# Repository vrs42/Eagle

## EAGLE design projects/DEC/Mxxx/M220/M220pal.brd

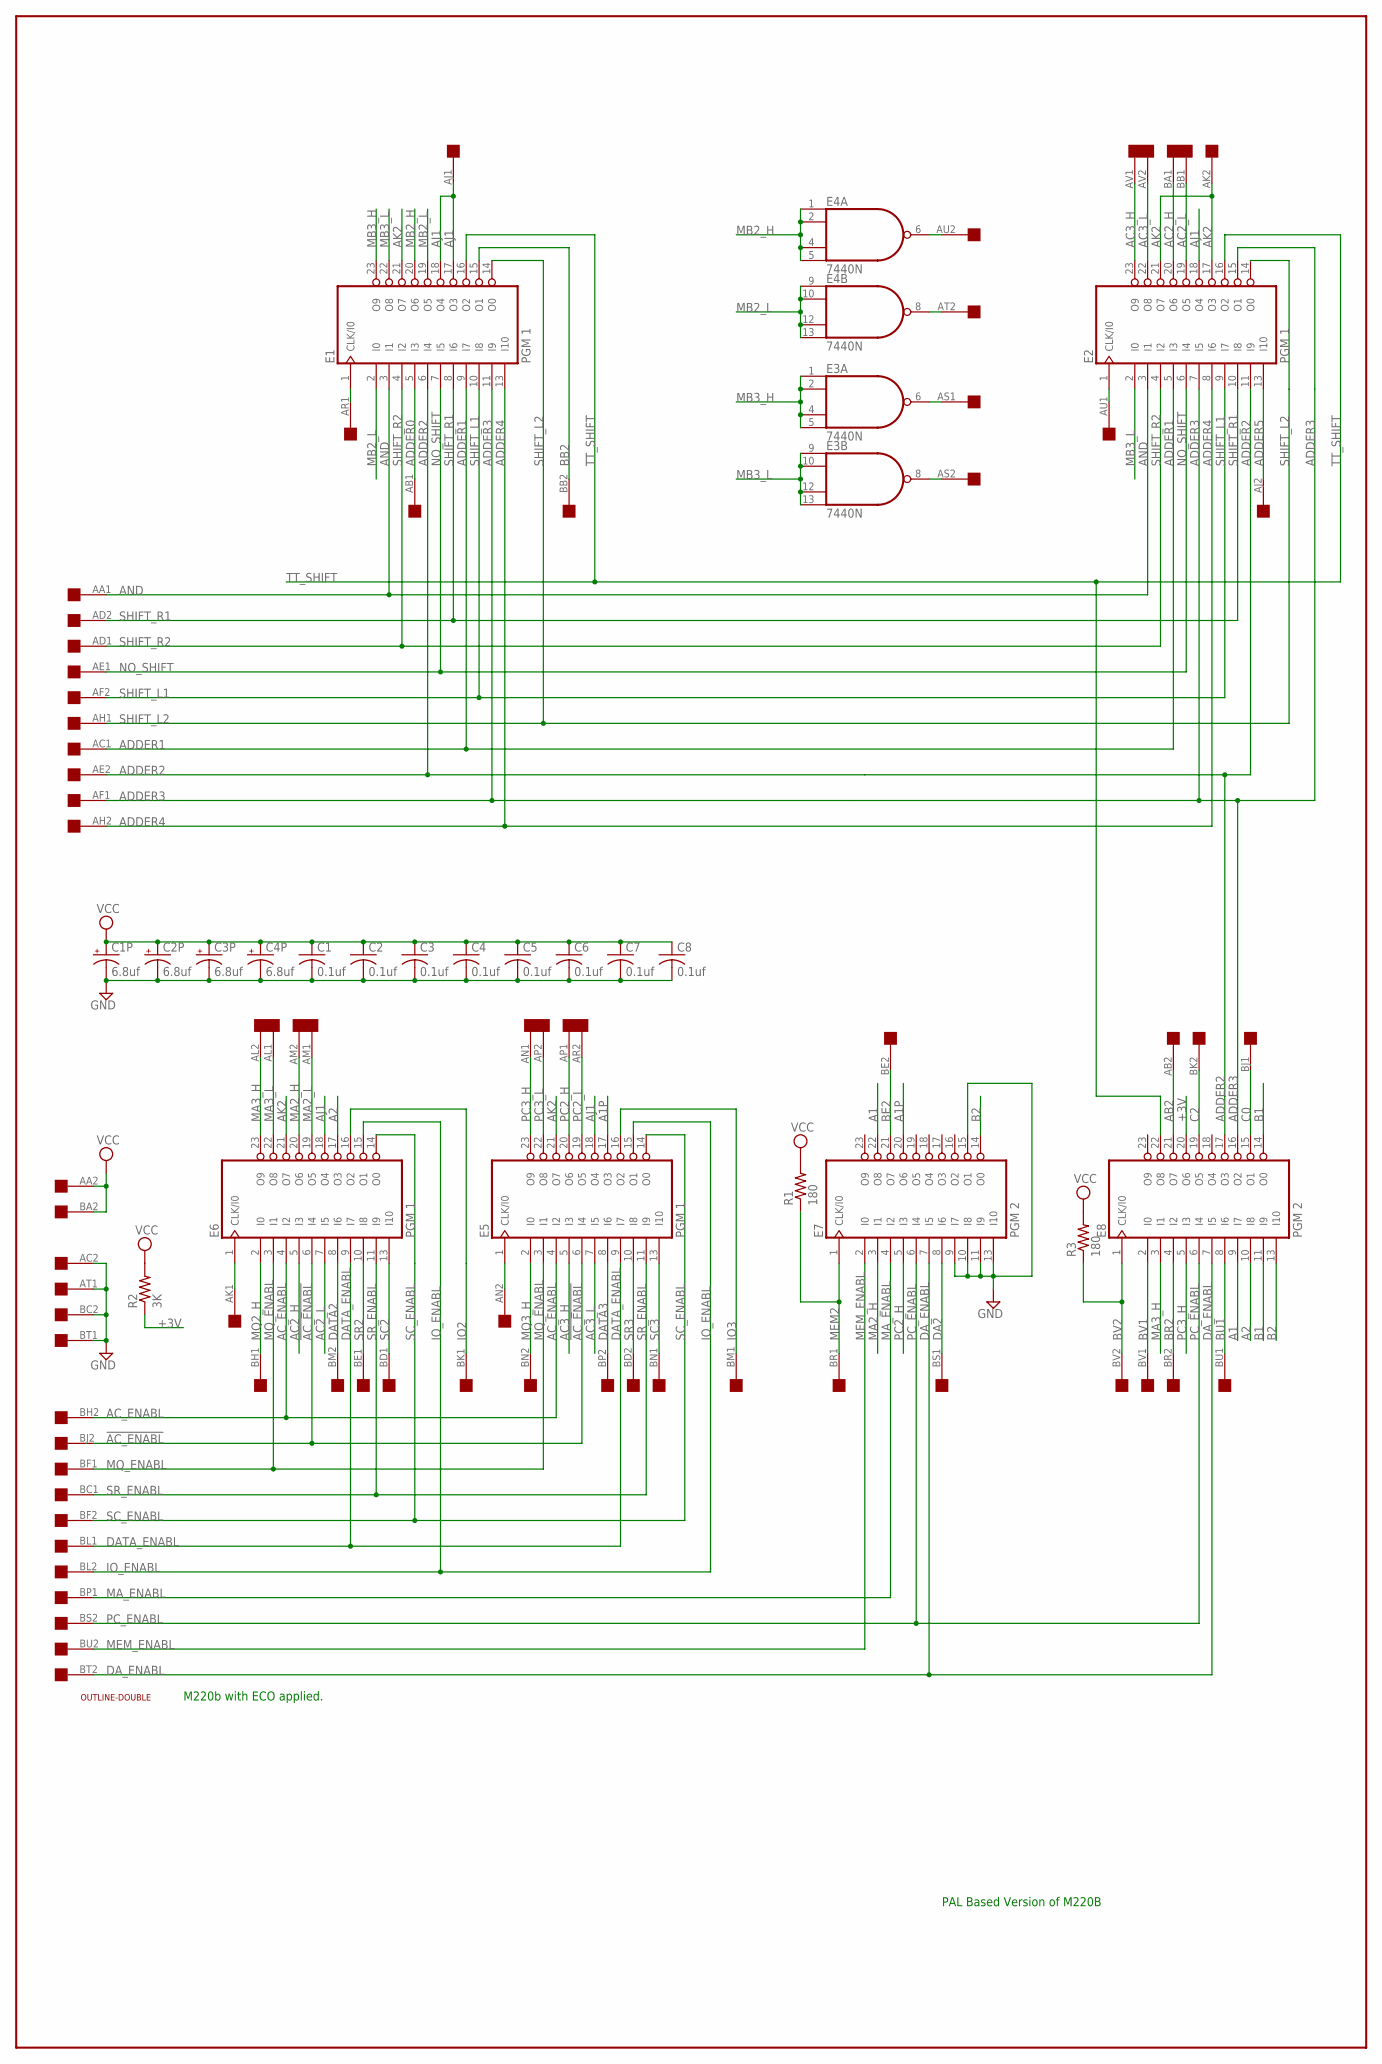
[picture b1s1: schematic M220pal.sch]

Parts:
C1, C2, C3, C4, C5, C6, C7, C8: 0.1uf; C050-025X075
C1P, C2P, C3P, C4P: 6.8uf; E15-5
E1, E2, E5, E6: PGM 1; DIL24-3
E3, E4: 7440N; DIL14
E7, E8: PGM 2; DIL24-3
R1, R3: 180; 0207/10
R2: 3K; 0207/10
U$1: DOUBLE; EDGE-CON4
U$2: OUTLINE-DOUBLE; DOUBLE

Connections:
!AC_ENABL: E5.6 (I4), E6.6 (I4), U$1.BJ2
+3V: E8.20 (O6), R2.1
A1: E7.22 (O8), E8.9 (I7)
A1P: E5.17 (O3), E7.20 (O6)
A2: E6.17 (O3), E8.10 (I8)
AB2: E8.21 (O7), U$1.AB2
AC2_H: E2.20 (O6), E6.5 (I3), U$1.BA1
AC2_L: E2.19 (O5), E6.7 (I5), U$1.BB1
AC3_H: E2.23 (O9), E5.5 (I3), U$1.AV1
AC3_L: E2.22 (O8), E5.7 (I5), U$1.AV2
AC_ENABL: E5.4 (I2), E6.4 (I2), U$1.BH2
ADDER0: E1.5 (I3), U$1.AB1
ADDER1: E1.9 (I7), E2.5 (I3), U$1.AC1
ADDER2: E1.6 (I4), E2.11 (I9), E8.17 (O3), U$1.AE2
ADDER3: E1.11 (I9), E2.7 (I5), E2.15 (O1), E8.16 (O2), U$1.AF1
ADDER4: E1.13 (I10), E2.8 (I6), U$1.AH2
ADDER5: E2.13 (I10), U$1.AJ2
AJ1: E1.17 (O3), E1.18 (O4), E2.18 (O4), E5.18 (O4), E6.18 (O4), U$1.AJ1
AK2: E1.21 (O7), E2.17 (O3), E2.21 (O7), E5.21 (O7), E6.21 (O7), U$1.AK2
AND: E1.3 (I1), E2.3 (I1), U$1.AA1
AS1: E3.6 (O), U$1.AS1
AS2: E3.8 (O), U$1.AS2
AT2: E4.8 (O), U$1.AT2
AU2: E4.6 (O), U$1.AU2
B1: E8.11 (I9), E8.14 (O0)
B2: E7.14 (O0), E8.13 (I10)
BB2: E1.15 (O1), U$1.BB2
BE2: E7.21 (O7), U$1.BE2
BR2: E8.4 (I2), U$1.BR2
BU1: E8.8 (I6), U$1.BU1
BV1: E8.2 (I0), U$1.BV1
BV2: E8.1 (CLK/I0), R3.1, U$1.BV2
C0: E8.15 (O1), U$1.BJ1
C2: E8.19 (O5), U$1.BK2
DA2: E7.8 (I6), U$1.BS1
DATA2: E6.8 (I6), U$1.BM2
DATA3: E5.8 (I6), U$1.BP2
DATA_ENABL: E5.9 (I7), E6.9 (I7), U$1.BL1
DA_ENABL: E7.7 (I5), E8.7 (I5), U$1.BT2
GND: C1.2, C1P.-, C2.2, C2P.-, C3.2, C3P.-, C4.2, C4P.-, C5.2, C6.2, C7.2, C8.2, E1.12 (GND), E2.12 (GND), E3.7 (GND), E4.7 (GND), E5.12 (GND), E6.12 (GND), E7.9 (I7), E7.10 (I8), E7.11 (I9), E7.12 (GND), E7.13 (I10), E7.15 (O1), E8.12 (GND), U$1.AC2, U$1.AT1, U$1.BC2, U$1.BT1
IO2: E6.16 (O2), U$1.BK1
IO3: E5.16 (O2), U$1.BM1
IO_ENABL: E5.15 (O1), E6.15 (O1), U$1.BL2
MA2_H: E6.20 (O6), E7.3 (I1), U$1.AM2
MA2_L: E6.19 (O5), U$1.AM1
MA3_H: E6.23 (O9), E8.3 (I1), U$1.AL2
MA3_L: E6.22 (O8), U$1.AL1
MA_ENABL: E7.4 (I2), U$1.BP1
MB2_H: E1.20 (O6), E4.1 (I0), E4.2 (I1), E4.4 (I2), E4.5 (I3)
MB2_L: E1.2 (I0), E1.19 (O5), E4.9 (I0), E4.10 (I1), E4.12 (I2), E4.13 (I3)
MB3_H: E1.23 (O9), E3.1 (I0), E3.2 (I1), E3.4 (I2), E3.5 (I3)
MB3_L: E1.22 (O8), E2.2 (I0), E3.9 (I0), E3.10 (I1), E3.12 (I2), E3.13 (I3)
MEM2: E7.1 (CLK/I0), R1.1, U$1.BR1
MEM_ENABL: E7.2 (I0), U$1.BU2
MQ2_H: E6.2 (I0), U$1.BH1
MQ3_H: E5.2 (I0), U$1.BN2
MQ_ENABL: E5.3 (I1), E6.3 (I1), U$1.BF1
unnamed: E6.1 (CLK/I0), U$1.AK1
unnamed: E5.1 (CLK/I0), U$1.AN2
unnamed: E1.1 (CLK/I0), U$1.AR1
unnamed: E2.1 (CLK/I0), U$1.AU1
NO_SHIFT: E1.7 (I5), E2.6 (I4), U$1.AE1
PC2_H: E5.20 (O6), E7.5 (I3), U$1.AP1
PC2_L: E5.19 (O5), U$1.AR2
PC3_H: E5.23 (O9), E8.5 (I3), U$1.AN1
PC3_L: E5.22 (O8), U$1.AP2
PC_ENABL: E7.6 (I4), E8.6 (I4), U$1.BS2
SC2: E6.13 (I10), U$1.BD1
SC3: E5.13 (I10), U$1.BN1
SC_ENABL: E5.14 (O0), E6.14 (O0), U$1.BF2
SHIFT_L1: E1.10 (I8), E2.9 (I7), U$1.AF2
SHIFT_L2: E1.14 (O0), E2.14 (O0), U$1.AH1
SHIFT_R1: E1.8 (I6), E2.10 (I8), U$1.AD2
SHIFT_R2: E1.4 (I2), E2.4 (I2), U$1.AD1
SR2: E6.10 (I8), U$1.BE1
SR3: E5.10 (I8), U$1.BD2
SR_ENABL: E5.11 (I9), E6.11 (I9), U$1.BC1
TT_SHIFT: E1.16 (O2), E2.16 (O2), E8.22 (O8)
VCC: C1.1, C1P.+, C2.1, C2P.+, C3.1, C3P.+, C4.1, C4P.+, C5.1, C6.1, C7.1, C8.1, E1.24 (VCC), E2.24 (VCC), E3.14 (VCC), E4.14 (VCC), E5.24 (VCC), E6.24 (VCC), E7.24 (VCC), E8.24 (VCC), R1.2, R2.2, R3.2, U$1.AA2, U$1.BA2

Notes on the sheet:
M220b with ECO applied.
PAL Based Version of M220B

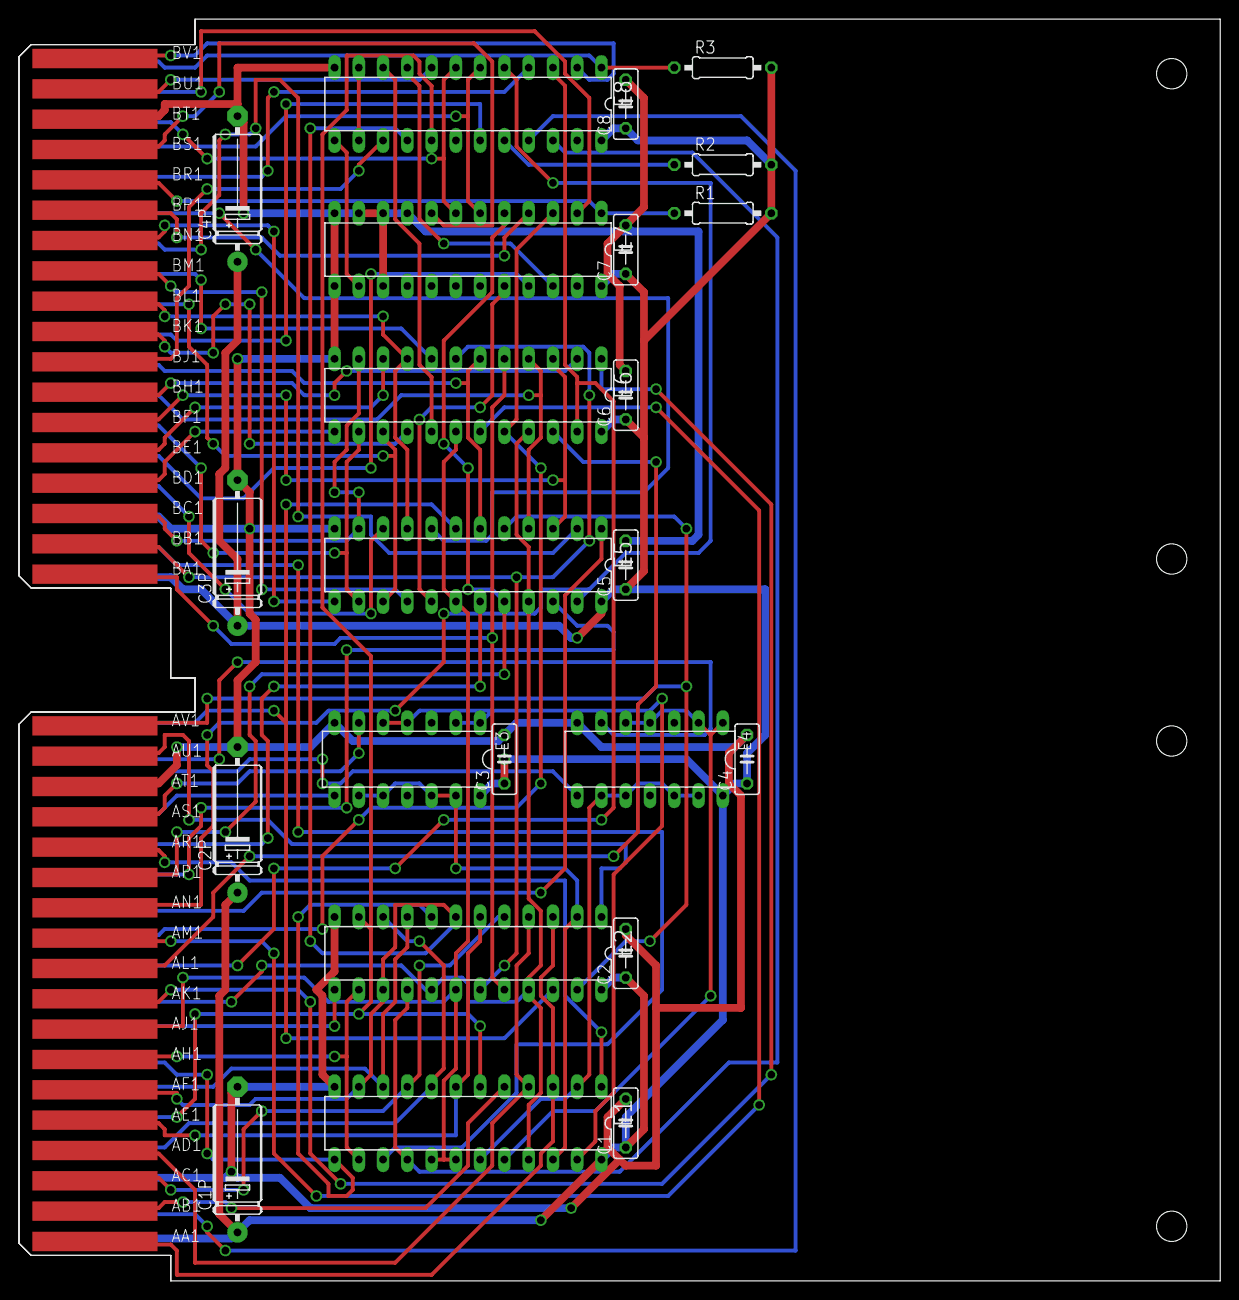
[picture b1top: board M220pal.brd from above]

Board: 2 copper layers, 125.7 x 132.1 mm, 25 parts (0 on the bottom side), 79 nets.

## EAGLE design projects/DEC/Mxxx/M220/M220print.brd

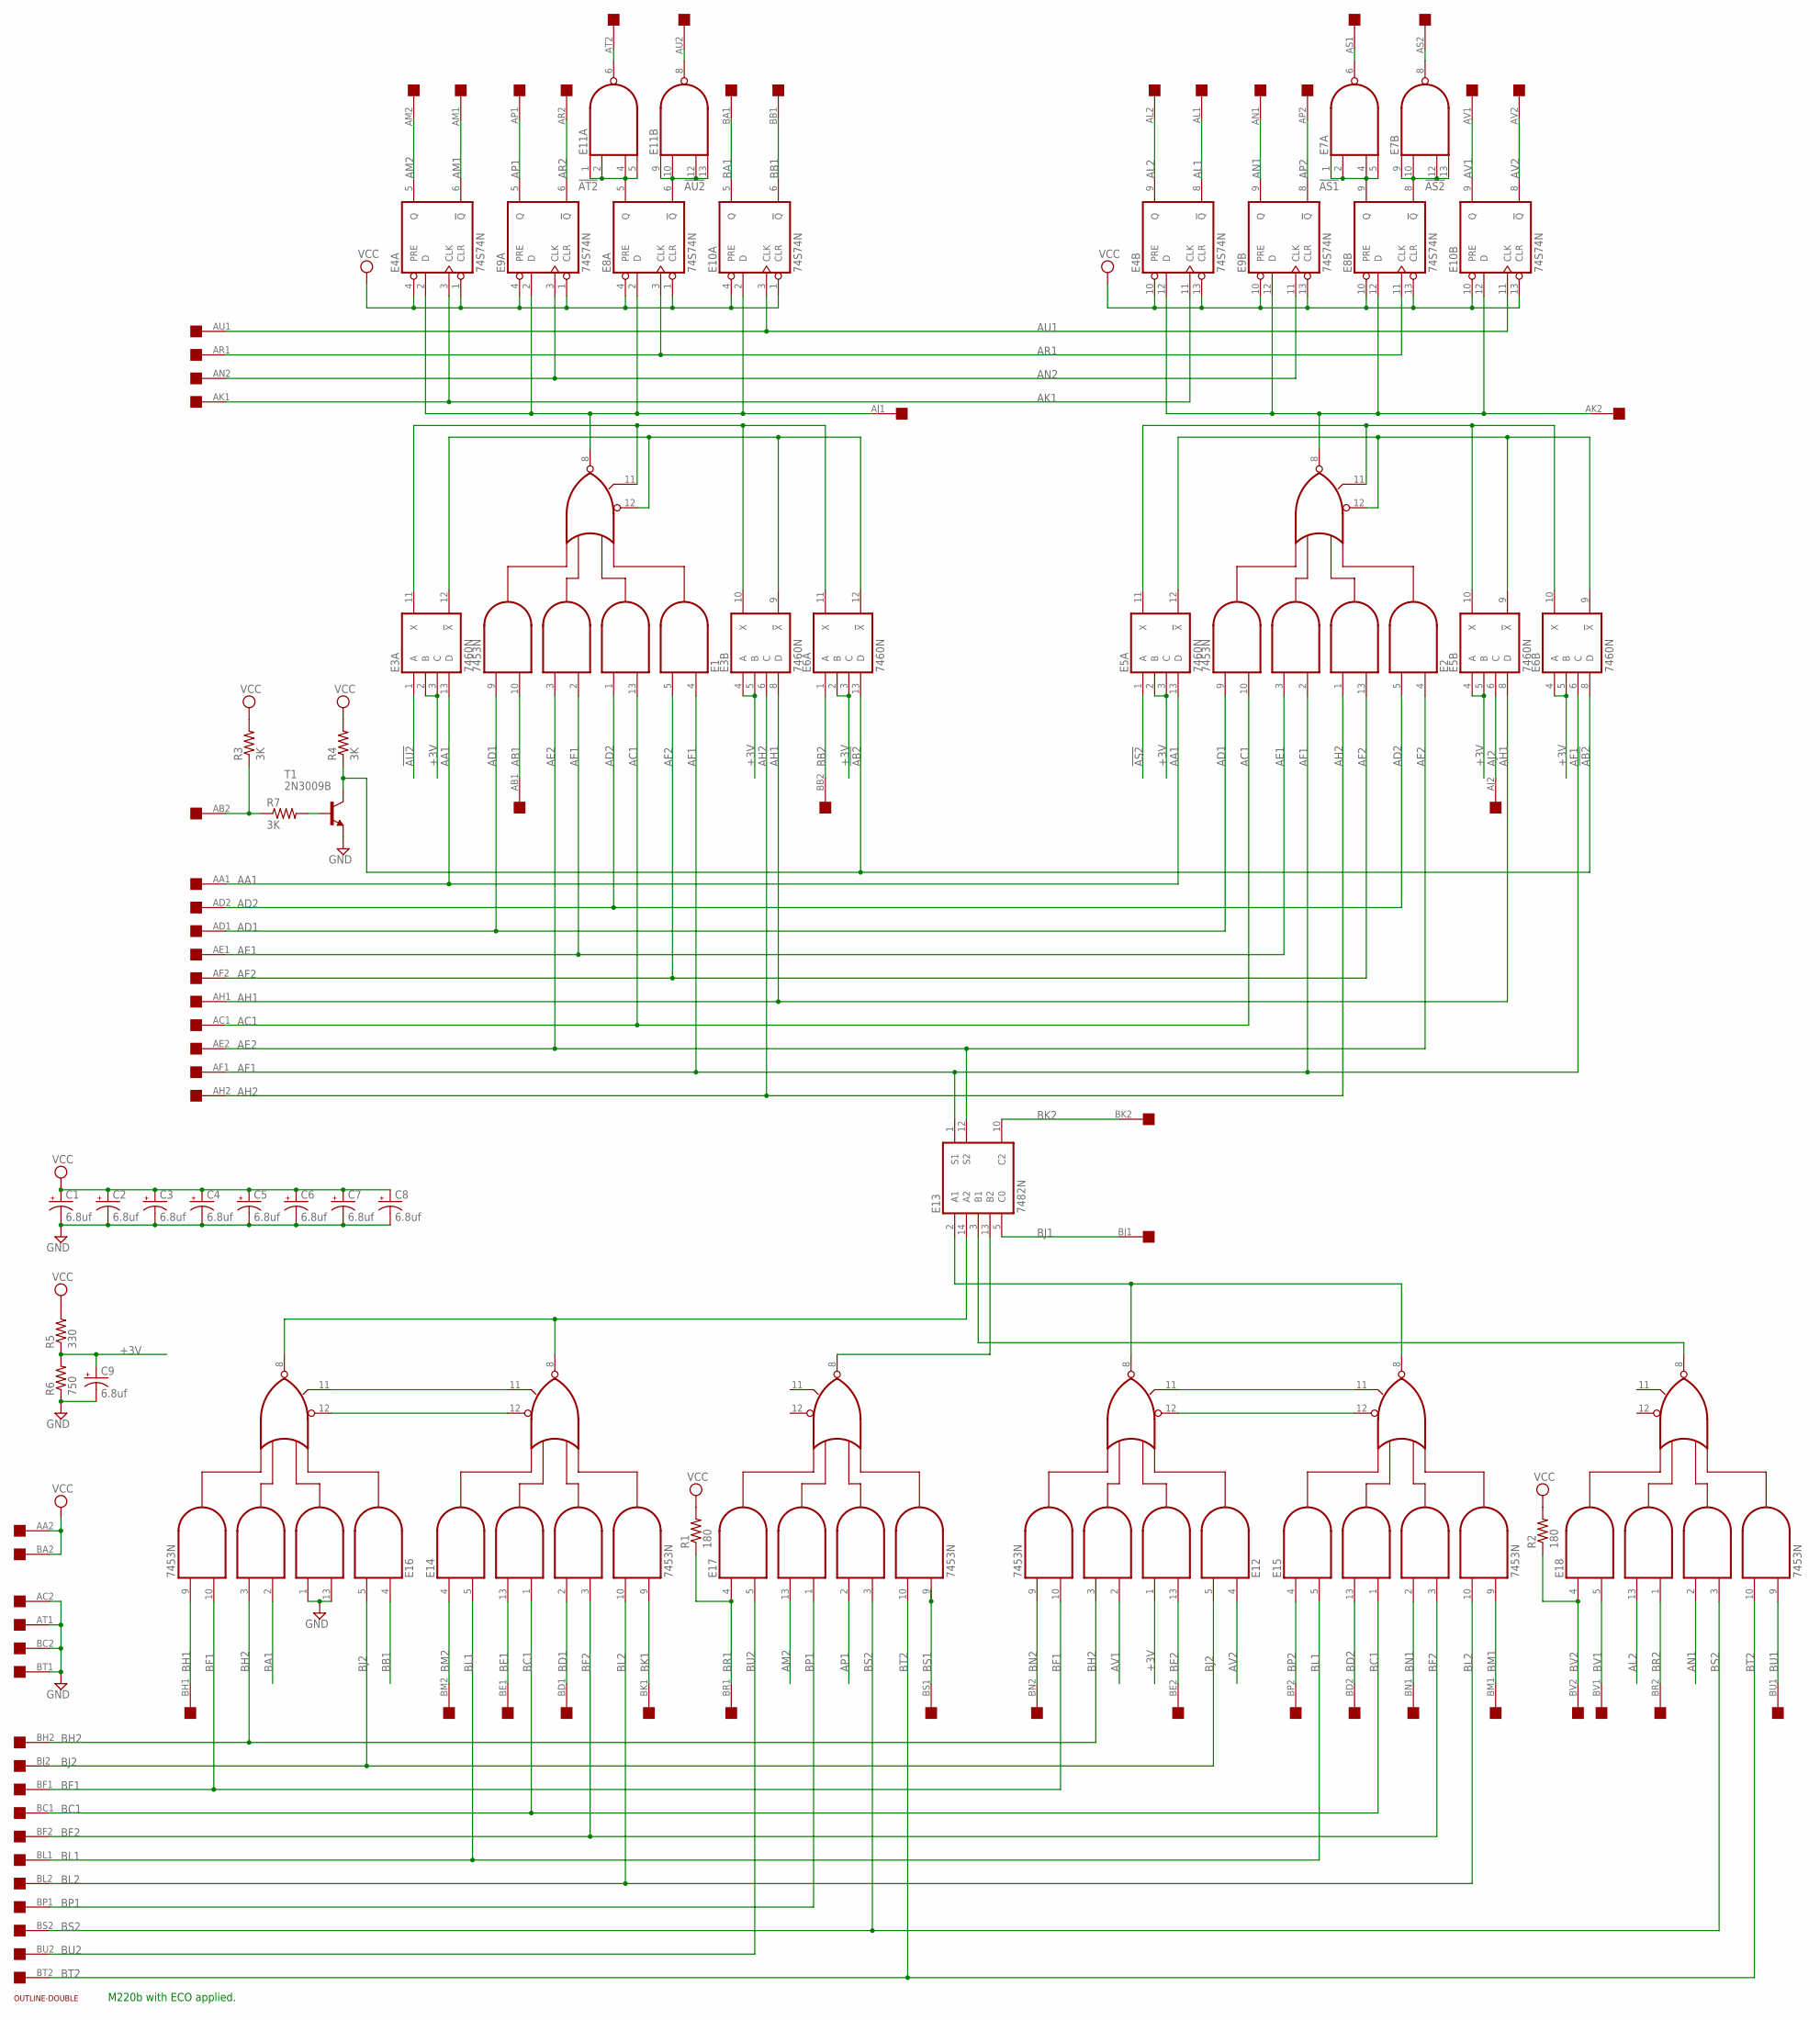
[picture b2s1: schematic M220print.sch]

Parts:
C1, C2, C3, C4, C5, C6, C7, C8, C9: 6.8uf; E15-5
E1, E2, E12, E14, E15, E16, E17, E18: 7453N; DIL14
E3, E5, E6: 7460N; DIL14
E4, E8, E9, E10: 74S74N; DIL14
E7, E11: 74S20N; DIL14
E13: 7482N; DIL14
R1, R2: 180; 0207/10
R3, R4, R7: 3K; 0207/10
R5: 330; 0207/10
R6: 750; 0207/10
T1: 2N3009B; TO5
U$1: DOUBLE; EDGE-CON4
U$2: OUTLINE-DOUBLE; DOUBLE

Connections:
!AB2: E6.8 (D), E6.13 (D), R4.1, T1.3 (C)
!AS1: E7.1 (I0), E7.2 (I1), E7.4 (I2), E7.5 (I3), E8.9 (Q)
!AS2: E5.1 (A), E7.9 (I0), E7.10 (I1), E7.12 (I2), E7.13 (I3), E8.8 (!Q)
!AT2: E8.5 (Q), E11.1 (I0), E11.2 (I1), E11.4 (I2), E11.5 (I3)
!AU2: E3.1 (A), E8.6 (!Q), E11.9 (I0), E11.10 (I1), E11.12 (I2), E11.13 (I3)
+3V: C9.+, E3.2 (B), E3.3 (C), E3.4 (A), E3.5 (B), E5.2 (B), E5.3 (C), E5.4 (A), E5.5 (B), E6.2 (B), E6.3 (C), E6.4 (A), E6.5 (B), E12.1 (I4), R5.1, R6.2
AA1: E3.13 (D), E5.13 (D), U$1.AA1
AB1: E1.10 (I7), U$1.AB1
AB2: R3.1, R7.1, U$1.AB2
AC1: E1.13 (I3), E2.10 (I7), U$1.AC1
AD1: E1.9 (I8), E2.9 (I8), U$1.AD1
AD2: E1.1 (I4), E2.5 (I2), U$1.AD2
AE1: E1.2 (I5), E2.3 (I6), U$1.AE1
AE2: E1.3 (I6), E2.4 (I1), E13.12 (S2), U$1.AE2
AF1: E1.4 (I1), E2.2 (I5), E6.6 (C), E13.1 (S1), U$1.AF1
AF2: E1.5 (I2), E2.13 (I3), U$1.AF2
AH1: E3.8 (D), E5.8 (D), U$1.AH1
AH2: E2.1 (I4), E3.6 (C), U$1.AH2
AJ1: E1.8 (O), E4.2 (D), E8.2 (D), E9.2 (D), E10.2 (D), U$1.AJ1
AJ2: E5.6 (C), U$1.AJ2
AK1: E4.3 (CLK), E4.11 (CLK), U$1.AK1
AK2: E2.8 (O), E4.12 (D), E8.12 (D), E9.12 (D), E10.12 (D), U$1.AK2
AL1: E4.8 (!Q), U$1.AL1
AL2: E4.9 (Q), E18.13 (I3), U$1.AL2
AM1: E4.6 (!Q), U$1.AM1
AM2: E4.5 (Q), E17.13 (I3), U$1.AM2
AN1: E9.9 (Q), E18.2 (I5), U$1.AN1
AN2: E9.3 (CLK), E9.11 (CLK), U$1.AN2
AP1: E9.5 (Q), E17.2 (I5), U$1.AP1
AP2: E9.8 (!Q), U$1.AP2
AR1: E8.3 (CLK), E8.11 (CLK), U$1.AR1
AR2: E9.6 (!Q), U$1.AR2
AS1: E7.6 (O), U$1.AS1
AS2: E7.8 (O), U$1.AS2
AT2: E11.6 (O), U$1.AT2
AU1: E10.3 (CLK), E10.11 (CLK), U$1.AU1
AU2: E11.8 (O), U$1.AU2
AV1: E10.9 (Q), E12.2 (I5), U$1.AV1
AV2: E10.8 (!Q), E12.4 (I1), U$1.AV2
BA1: E10.5 (Q), E16.2 (I5), U$1.BA1
BB1: E10.6 (!Q), E16.4 (I1), U$1.BB1
BB2: E6.1 (A), U$1.BB2
BC1: E14.1 (I4), E15.1 (I4), U$1.BC1
BD1: E14.2 (I5), U$1.BD1
BD2: E15.13 (I3), U$1.BD2
BE1: E14.13 (I3), U$1.BE1
BE2: E12.13 (I3), U$1.BE2
BF1: E12.10 (I7), E16.10 (I7), U$1.BF1
BF2: E14.3 (I6), E15.3 (I6), U$1.BF2
BH1: E16.9 (I8), U$1.BH1
BH2: E12.3 (I6), E16.3 (I6), U$1.BH2
BJ1: E13.5 (C0), U$1.BJ1
BJ2: E12.5 (I2), E16.5 (I2), U$1.BJ2
BK1: E14.9 (I8), U$1.BK1
BK2: E13.10 (C2), U$1.BK2
BL1: E14.5 (I2), E15.5 (I2), U$1.BL1
BL2: E14.10 (I7), E15.10 (I7), U$1.BL2
BM1: E15.9 (I8), U$1.BM1
BM2: E14.4 (I1), U$1.BM2
BN1: E15.2 (I5), U$1.BN1
BN2: E12.9 (I8), U$1.BN2
BP1: E17.1 (I4), U$1.BP1
BP2: E15.4 (I1), U$1.BP2
BR1: E17.4 (I1), R1.1, U$1.BR1
BR2: E18.1 (I4), U$1.BR2
BS1: E17.9 (I8), U$1.BS1
BS2: E17.3 (I6), E18.3 (I6), U$1.BS2
BT2: E17.10 (I7), E18.10 (I7), U$1.BT2
BU1: E18.9 (I8), U$1.BU1
BU2: E17.5 (I2), U$1.BU2
BV1: E18.5 (I2), U$1.BV1
BV2: E18.4 (I1), R2.1, U$1.BV2
GND: C1.-, C2.-, C3.-, C4.-, C5.-, C6.-, C7.-, C8.-, C9.-, E1.7 (GND), E2.7 (GND), E3.7 (GND), E4.7 (GND), E5.7 (GND), E6.7 (GND), E7.7 (GND), E8.7 (GND), E9.7 (GND), E10.7 (GND), E11.7 (GND), E12.7 (GND), E13.7 (GND), E14.7 (GND), E15.7 (GND), E16.1 (I4), E16.7 (GND), E16.13 (I3), E17.7 (GND), E18.7 (GND), R6.1, T1.1 (E), U$1.AC2, U$1.AT1, U$1.BC2, U$1.BT1
unnamed: E12.12 (I9), E15.12 (I9)
unnamed: R7.2, T1.2 (B)
unnamed: E12.11 (I10), E15.11 (I10)
unnamed: E13.14 (A2), E14.8 (O), E16.8 (O)
unnamed: E14.11 (I10), E16.11 (I10)
unnamed: E14.12 (I9), E16.12 (I9)
unnamed: E12.8 (O), E13.2 (A1), E15.8 (O)
unnamed: E2.12 (I9), E5.9 (!X), E5.12 (!X), E6.9 (!X)
unnamed: E1.12 (I9), E3.9 (!X), E3.12 (!X), E6.12 (!X)
unnamed: E2.11 (I10), E5.10 (X), E5.11 (X), E6.10 (X)
unnamed: E13.13 (B2), E17.8 (O)
unnamed: E1.11 (I10), E3.10 (X), E3.11 (X), E6.11 (X)
unnamed: E13.3 (B1), E18.8 (O)
VCC: C1.+, C2.+, C3.+, C4.+, C5.+, C6.+, C7.+, C8.+, E1.14 (VCC), E2.14 (VCC), E3.14 (VCC), E4.1 (CLR), E4.4 (PRE), E4.10 (PRE), E4.13 (CLR), E4.14 (VCC), E5.14 (VCC), E6.14 (VCC), E7.14 (VCC), E8.1 (CLR), E8.4 (PRE), E8.10 (PRE), E8.13 (CLR), E8.14 (VCC), E9.1 (CLR), E9.4 (PRE), E9.10 (PRE), E9.13 (CLR), E9.14 (VCC), E10.1 (CLR), E10.4 (PRE), E10.10 (PRE), E10.13 (CLR), E10.14 (VCC), E11.14 (VCC), E12.14 (VCC), E13.4 (VCC), E14.14 (VCC), E15.14 (VCC), E16.14 (VCC), E17.14 (VCC), E18.14 (VCC), R1.2, R2.2, R3.2, R4.2, R5.2, U$1.AA2, U$1.BA2

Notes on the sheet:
M220b with ECO applied.

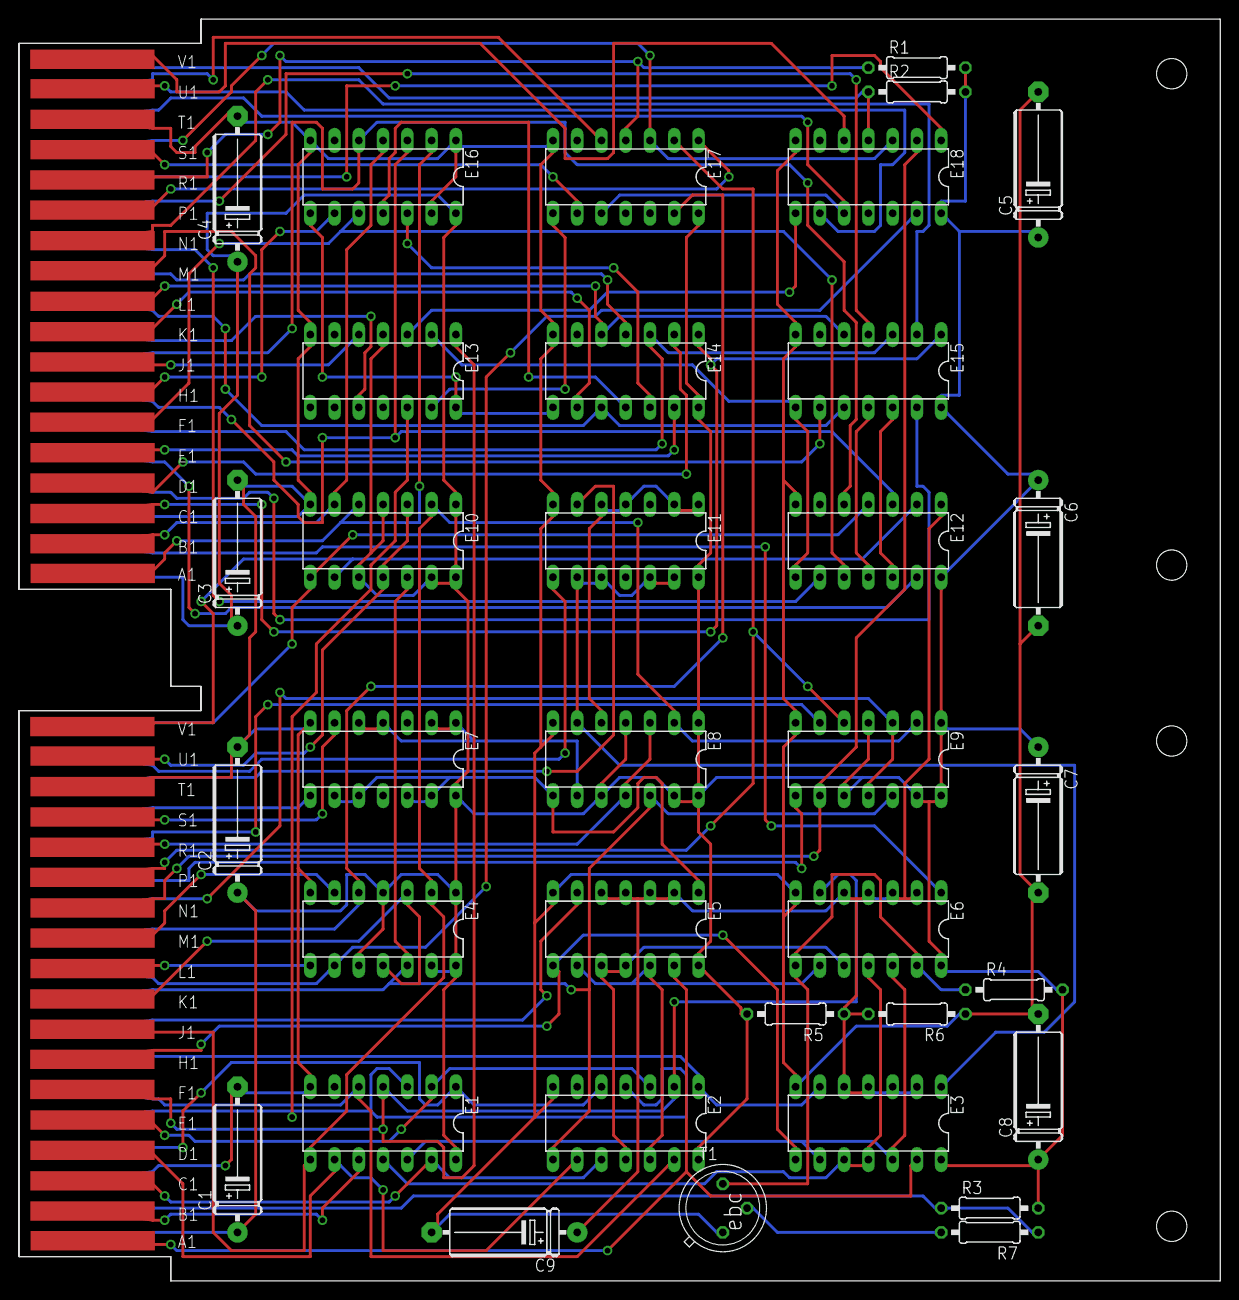
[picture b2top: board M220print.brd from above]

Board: 2 copper layers, 125.7 x 132.1 mm, 37 parts (0 on the bottom side), 87 nets.

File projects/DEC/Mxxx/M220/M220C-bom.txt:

Partlist exported from C:/Users/Vince/Documents/Eagle/projects/DEC/Mxxx/M220/M220C.sch at 12/9/2017 4:49:37 PM

Qty Value          Device            Package   Parts                                Description                                                     
1                  DOUBLE            EDGE-CON4 U$1                                  Double-Height DEC board                                         
2   180            R-US_0207/10      0207/10   R1, R2                               RESISTOR, American symbol                                       
1   2N3009B        2N1613            TO5       T1                                   NPN TRANSISTOR                                                  
1   330            R-US_0207/10      0207/10   R6                                   RESISTOR, American symbol                                       
3   3K             R-US_0207/10      0207/10   R3, R4, R5                           RESISTOR, American symbol                                       
9   6.8uf          CPOL-USE15-5AXIAL E15-5     C1, C2, C3, C4, C5, C6, C7, C8, C9   0.6" veresion of an electrolytic                                
2   7440N          74S20N            DIL14     E7, E11                              Dual 4-input NAND gate                                          
8   7453N          7453N             DIL14     E1, E2, E12, E14, E15, E16, E17, E18 4-2-3-2 input AND OR INVERTER gates                             
3   7460N          7460N             DIL14     E3, E5, E6                           Dual 4-input EXPANDER                                           
4   7474N          74S74N            DIL14     E4, E8, E9, E10                      Dual D type positive edge triggered FLIP FLOP, preset and clear 
1   7482N          7482N             DIL14     E13                                  2-bit binary full ADDER                                         
1   750            R-US_0207/10      0207/10   R7                                   RESISTOR, American symbol                                       
1   OUTLINE-DOUBLE OUTLINE-DOUBLE    DOUBLE    U$2                                  Board outlines for DEC boards.

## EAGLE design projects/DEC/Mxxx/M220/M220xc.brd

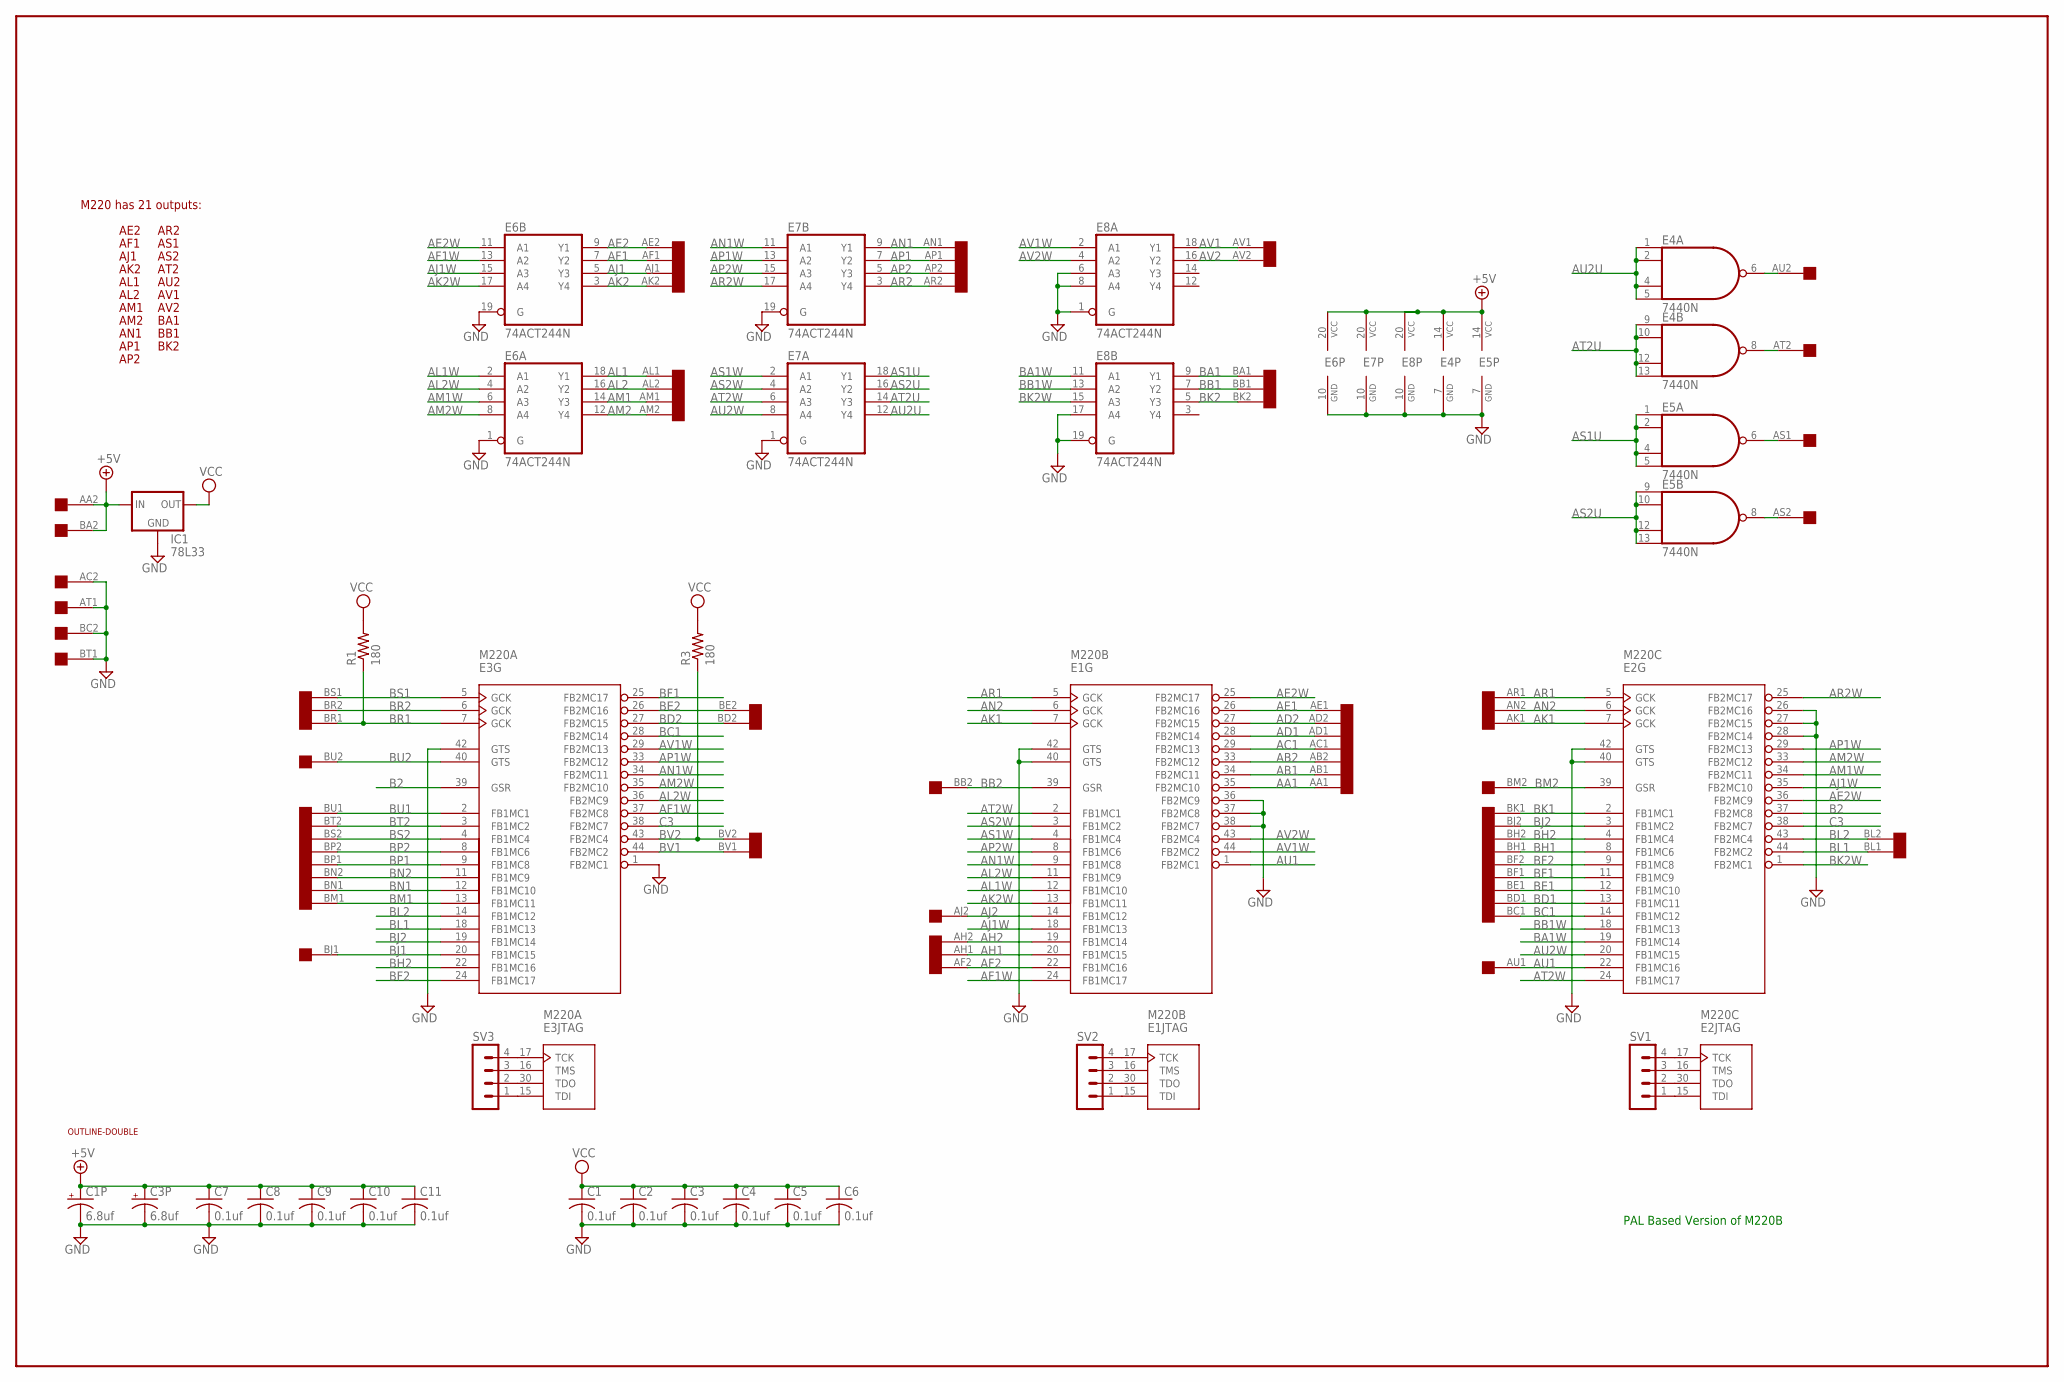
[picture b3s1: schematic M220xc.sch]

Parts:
C1, C2, C3, C4, C5, C6, C7, C8, C9, C10, C11: 0.1uf; C050-025X075
C1P, C3P: 6.8uf; E15-5
E1: M220B; PLCC-S44
E2: M220C; PLCC-S44
E3: M220A; PLCC-S44
E4, E5: 7440N; DIL14
E6, E7, E8: 74ACT244N; DIL20
IC1: 78L33; 78LXX
R1, R3: 180; 0207/10
SV1, SV2, SV3: MA04-1
U$1: DOUBLE; EDGE-CON4
U$2: OUTLINE-DOUBLE; DOUBLE

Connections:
+5V: C1P.+, C3P.+, C7.1, C8.1, C9.1, C10.1, C11.1, E4.14 (VCC), E5.14 (VCC), E6.20 (VCC), E7.20 (VCC), E8.20 (VCC), IC1.IN, U$1.AA2, U$1.BA2
AA1: E1.35 (FB2MC10), U$1.AA1
AB1: E1.34 (FB2MC11), U$1.AB1
AB2: E1.33 (FB2MC12), U$1.AB2
AC1: E1.29 (FB2MC13), U$1.AC1
AD1: E1.28 (FB2MC14), U$1.AD1
AD2: E1.27 (FB2MC15), U$1.AD2
AE1: E1.26 (FB2MC16), U$1.AE1
AE2: E6.9 (Y1), U$1.AE2
AE2W: E1.25 (FB2MC17), E2.36 (FB2MC9), E6.11 (A1)
AF1: E6.7 (Y2), U$1.AF1
AF1W: E1.24 (FB1MC17), E3.37 (FB2MC8), E6.13 (A2)
AF2: E1.22 (FB1MC16), U$1.AF2
AH1: E1.20 (FB1MC15), U$1.AH1
AH2: E1.19 (FB1MC14), U$1.AH2
AJ1: E6.5 (Y3), U$1.AJ1
AJ1W: E1.18 (FB1MC13), E2.35 (FB2MC10), E6.15 (A3)
AJ2: E1.14 (FB1MC12), U$1.AJ2
AK1: E1.7 (GCK), E2.7 (GCK), U$1.AK1
AK2: E6.3 (Y4), U$1.AK2
AK2W: E1.13 (FB1MC11), E6.17 (A4)
AL1: E6.18 (Y1), U$1.AL1
AL1W: E1.12 (FB1MC10), E6.2 (A1)
AL2: E6.16 (Y2), U$1.AL2
AL2W: E1.11 (FB1MC9), E3.36 (FB2MC9), E6.4 (A2)
AM1: E6.14 (Y3), U$1.AM1
AM1W: E2.34 (FB2MC11), E6.6 (A3)
AM2: E6.12 (Y4), U$1.AM2
AM2W: E2.33 (FB2MC12), E3.35 (FB2MC10), E6.8 (A4)
AN1: E7.9 (Y1), U$1.AN1
AN1W: E1.9 (FB1MC8), E3.34 (FB2MC11), E7.11 (A1)
AN2: E1.6 (GCK), E2.6 (GCK), U$1.AN2
AP1: E7.7 (Y2), U$1.AP1
AP1W: E2.29 (FB2MC13), E3.33 (FB2MC12), E7.13 (A2)
AP2: E7.5 (Y3), U$1.AP2
AP2W: E1.8 (FB1MC6), E7.15 (A3)
AR1: E1.5 (GCK), E2.5 (GCK), U$1.AR1
AR2: E7.3 (Y4), U$1.AR2
AR2W: E2.25 (FB2MC17), E7.17 (A4)
AS1: E5.6 (O), U$1.AS1
AS1U: E5.1 (I0), E5.2 (I1), E5.4 (I2), E5.5 (I3), E7.18 (Y1)
AS1W: E1.4 (FB1MC4), E7.2 (A1)
AS2: E5.8 (O), U$1.AS2
AS2U: E5.9 (I0), E5.10 (I1), E5.12 (I2), E5.13 (I3), E7.16 (Y2)
AS2W: E1.3 (FB1MC2), E7.4 (A2)
AT2: E4.8 (O), U$1.AT2
AT2U: E4.9 (I0), E4.10 (I1), E4.12 (I2), E4.13 (I3), E7.14 (Y3)
AT2W: E1.2 (FB1MC1), E2.24 (FB1MC17), E7.6 (A3)
AU1: E1.1 (FB2MC1), E2.22 (FB1MC16), U$1.AU1
AU2: E4.6 (O), U$1.AU2
AU2U: E4.1 (I0), E4.2 (I1), E4.4 (I2), E4.5 (I3), E7.12 (Y4)
AU2W: E2.20 (FB1MC15), E7.8 (A4)
AV1: E8.18 (Y1), U$1.AV1
AV1W: E1.44 (FB2MC2), E3.29 (FB2MC13), E8.2 (A1)
AV2: E8.16 (Y2), U$1.AV2
AV2W: E1.43 (FB2MC4), E8.4 (A2)
B2: E2.37 (FB2MC8), E3.39 (GSR)
BA1: E8.9 (Y1), U$1.BA1
BA1W: E2.19 (FB1MC14), E8.11 (A1)
BB1: E8.7 (Y2), U$1.BB1
BB1W: E2.18 (FB1MC13), E8.13 (A2)
BB2: E1.39 (GSR), U$1.BB2
BC1: E2.14 (FB1MC12), E3.28 (FB2MC14), U$1.BC1
BD1: E2.13 (FB1MC11), U$1.BD1
BD2: E3.27 (FB2MC15), U$1.BD2
BE1: E2.12 (FB1MC10), U$1.BE1
BE2: E3.26 (FB2MC16), U$1.BE2
BF1: E2.11 (FB1MC9), E3.25 (FB2MC17), U$1.BF1
BF2: E2.9 (FB1MC8), E3.24 (FB1MC17), U$1.BF2
BH1: E2.8 (FB1MC6), U$1.BH1
BH2: E2.4 (FB1MC4), E3.22 (FB1MC16), U$1.BH2
BJ1: E3.20 (FB1MC15), U$1.BJ1
BJ2: E2.3 (FB1MC2), E3.19 (FB1MC14), U$1.BJ2
BK1: E2.2 (FB1MC1), U$1.BK1
BK2: E8.5 (Y3), U$1.BK2
BK2W: E2.1 (FB2MC1), E8.15 (A3)
BL1: E2.44 (FB2MC2), E3.18 (FB1MC13), U$1.BL1
BL2: E2.43 (FB2MC4), E3.14 (FB1MC12), U$1.BL2
BM1: E3.13 (FB1MC11), U$1.BM1
BM2: E2.39 (GSR), U$1.BM2
BN1: E3.12 (FB1MC10), U$1.BN1
BN2: E3.11 (FB1MC9), U$1.BN2
BP1: E3.9 (FB1MC8), U$1.BP1
BP2: E3.8 (FB1MC6), U$1.BP2
BR1: E3.7 (GCK), R1.1, U$1.BR1
BR2: E3.6 (GCK), U$1.BR2
BS1: E3.5 (GCK), U$1.BS1
BS2: E3.4 (FB1MC4), U$1.BS2
BT2: E3.3 (FB1MC2), U$1.BT2
BU1: E3.2 (FB1MC1), U$1.BU1
BU2: E3.40 (GTS), U$1.BU2
BV1: E3.44 (FB2MC2), U$1.BV1
BV2: E3.43 (FB2MC4), R3.1, U$1.BV2
C3: E2.38 (FB2MC7), E3.38 (FB2MC7)
GND: C1.2, C1P.-, C2.2, C3.2, C3P.-, C4.2, C5.2, C6.2, C7.2, C8.2, C9.2, C10.2, C11.2, E1.10 (GND), E1.23 (GND), E1.31 (GND), E1.36 (FB2MC9), E1.37 (FB2MC8), E1.38 (FB2MC7), E1.40 (GTS), E1.42 (GTS), E2.10 (GND), E2.23 (GND), E2.26 (FB2MC16), E2.27 (FB2MC15), E2.28 (FB2MC14), E2.31 (GND), E2.40 (GTS), E2.42 (GTS), E3.1 (FB2MC1), E3.10 (GND), E3.23 (GND), E3.31 (GND), E3.42 (GTS), E4.7 (GND), E5.7 (GND), E6.1 (G), E6.10 (GND), E6.19 (G), E7.1 (G), E7.10 (GND), E7.19 (G), E8.1 (G), E8.6 (A3), E8.8 (A4), E8.10 (GND), E8.17 (A4), E8.19 (G), IC1.GND, U$1.AC2, U$1.AT1, U$1.BC2, U$1.BT1
unnamed: E1.15 (TDI), SV2.1
unnamed: E1.30 (TDO), SV2.2
unnamed: E2.15 (TDI), SV1.1
unnamed: E1.16 (TMS), SV2.3
unnamed: E2.30 (TDO), SV1.2
unnamed: E2.16 (TMS), SV1.3
unnamed: E2.17 (TCK), SV1.4
unnamed: E1.17 (TCK), SV2.4
unnamed: E3.15 (TDI), SV3.1
unnamed: E3.30 (TDO), SV3.2
unnamed: E3.16 (TMS), SV3.3
unnamed: E3.17 (TCK), SV3.4
VCC: C1.1, C2.1, C3.1, C4.1, C5.1, C6.1, E1.21 (VCC), E1.32 (VCC), E1.41 (VCC), E2.21 (VCC), E2.32 (VCC), E2.41 (VCC), E3.21 (VCC), E3.32 (VCC), E3.41 (VCC), IC1.OUT, R1.2, R3.2

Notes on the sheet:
PAL Based Version of M220B
M220 has 21 outputs:
AE2
BK2
AM1
AM2
AP1
AR2
AT2
AU2
BA1
BB1
AJ1
AK2
AN1
AL2
AS2
AV1
AP2
AL1
AS1
AV2
AF1
